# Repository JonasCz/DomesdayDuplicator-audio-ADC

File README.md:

# An experiment to add an audio ADC to the Domesday Duplicator (DdD)

An extension to the DdD to to add synced baseband audio support, with the DdD capture app writing it as a separate WAV file. Both PCM1802 (common module from china or custom board), or using the built-in adc128s102 that is already integrated on the DE0-nano board. PCM1802 has better quality, integrated ADC notably has a high noise floor at -40dB.

## Setup:

### You can use either:

**Custom board**: I designed a custom board, which has RCAs for both the PCM 1802, and the integrated adc128s102, allowing to use 4 channels at the same time if desired. Has better power regulator than PCM1802 modules (maybe lower noise), has a DIP switch for -10dB input level if needed.

Contact @Doohickey in Domesday86 discord, for around €20 + cheap shipping in europe.

**PCM1802 module**:

You can also use the low cost PCM1802 module. Connect with jumper wires, diagram:

Wires between pcm1802 and DdD should be as short as possible. You don't need to solder any of the fmt/mode/osr/bypass. Make sure the 3.3v on your module is working (3.3v is present), 3.3v needs to be connected to the pdw and fsy pins on the module. Connect lin/rin/gnd on the module to your audio source.

**adc128s102**:

Can be used with just some resistors and capacitors:

Resistors: any value between 1k and 10k works. Capacitor 1-10uF works. All capacitors and resistors need to be the same.

Can be used together with PCM1802 for 4 channels.

## Firmware:

You'll need to flash the firmware of the deo-nano, using the same process as for the initial flash. (firmware file in releases section). Note that there's no backward compatiblity, both the firmware and application need to be from this repository. Firmware from this repository won't work with old application either.

## Application:

Set your audio source in the application settings, then start capturing. It will write a wav file in the same location as the RF data, and show some statistics for the audio. The application is missing the logo in the UI because I couldn't get it to work, it's not intentionally removed :-)

(original readme follows)

# Domesday Duplicator (DdD)

Please see the [Project Wiki](https://github.com/simoninns/DomesdayDuplicator/wiki) for details of the project and for access to the project documentation.

The Domesday Duplicator is a LaserDisc capture focused, USB 3.0 based DAQ capable of 40 million samples per second acquisition of analogue RF data at 10-bits resolution, the data being in generic PCM style stream format is ready for [FLAC compression](https://github.com/oyvindln/vhs-decode/wiki/RF-Compression-&-Decompression-Guide) or direct use with a wide range of decoders.

Capture is via a easy to use GUI capture application.

# The Decode Family 

The samples the DdD capture can be used with the family of decoders that make the FM RF Archival workflow ready to use today.

[LaserDisc Decode](https://github.com/happycube/ld-decode) / [VHS-Decode (Videotape)](https://github.com/oyvindln/vhs-decode/wiki/) / [CVBS (Composite) Decode](CVBS-Composite-Decode) / [HiFi Decode](HiFi-Decode) / [RTLSDR HiFi Decode](RTLSDR) / [MUSE-Decode](https://bitbucket.org/staffanulfberg/ldaudio/src/master/musecpp/) / [CD-Decode](https://github.com/happycube/cd-decode) / [FL2K TBC Player](TBC-To-Analogue)

# 3D Printed Case 

The DomesDay Duplicator also has a [3D models](https://github.com/simoninns/DomesdayDuplicator-Case) and ready to use data for producing 3D printed cases, to protect from dust or line with copper tape for affordable EMI shielding for example.

## Authors

Domesday Duplicator was written & designed by [Simon Inns](https://github.com/simoninns).

Current documentation & fabrication is maintained by [Harry Munday](https://github.com/harrypm). 

## Licences

- [Software License - (Creative Commons BY-SA 4.0)](https://github.com/simoninns/DomesdayDuplicator/blob/master/LICENSE)
- [Hardware License - (GPLv3)](https://creativecommons.org/licenses/by-sa/4.0/)

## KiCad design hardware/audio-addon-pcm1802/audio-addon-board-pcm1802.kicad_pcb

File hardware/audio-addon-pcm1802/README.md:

# Audio capture and the PCM1802 add-on board

The Domesday Duplicator can record a player's baseband analogue audio at the same time as the
RF, written to separate files next to the RF capture. The audio is sampled in lock-step with
the RF: the gateware reads the audio converters once per 512-sample frame of the RF stream,
so the two can be lined up exactly afterwards without any clock-drift correction.

This needs three things:

1. one or both audio converters connected to the DE0-NANO (below);
2. the audio-capable application gateware, which sends the RF stream in the framed sample
   format (specified with the gateware, under [fpga/](../../fpga/)) instead of the plain
   sequence-counter format;
3. the capture application, with **File → Settings → Capture → Audio** set to the converters
   in use (or `--audio-source` on the command line).

With gateware that does not send the framed format, the capture application captures RF
exactly as before and reports that audio is not available from the device.

## Converters

There are two, and they can be used together for four channels.

| | PCM1802 | ADC128S022 |
| --- | --- | --- |
| Where | External — this add-on board, or a low-cost module | Already on the DE0-NANO |
| Resolution | 24-bit | 12-bit |
| Quality | The one to use | Noise floor around −40 dB; a fallback |
| Output file | `<capture>_audio_external_adc.s24` | `<capture>_audio_integrated_adc.s16` |

Both files are headerless, little-endian, interleaved stereo (left first). The sample rate is
the RF sample rate divided by 512: **78125 Hz** for a 40 MSPS capture, and **39062.5 Hz** when
the gateware's 2:1 decimation (20 MSPS) is on. The capture's metadata records the exact rate.

## The add-on board

This directory holds the design of a small board that plugs onto the DE0-NANO's 2x13 header
(JP3) and carries both audio paths:

- the **PCM1802** with RCA inputs, its own supply regulator and a DIP switch for a −10 dB
  input pad;
- RCA inputs and the bias network for the DE0-NANO's own **ADC128S022**.

| Path | Contents |
| --- | --- |
| `audio-addon-board-pcm1802.kicad_pro` / `.kicad_sch` / `.kicad_pcb` | KiCad 9 project: schematic and layout |
| `audio-addon-board-pcm1802-rounded.*` | The same layout with rounded tracks, generated by the round-tracks plugin |
| `parts/` | Symbols, footprints and 3D models that are not in the KiCad standard libraries |
| `production/` | Fabrication outputs for the built board: BOM, placement, designators and IPC netlist |
| `fabrication-toolkit-options.json`, `*.round-tracks-config` | Settings for the KiCad plugins that produced the above |
| `images/` | The photographs and wiring diagrams on this page |

### Connection to the DE0-NANO

All signals use the DE0-NANO's 2x13 header (JP3); nothing on the Duplicator main board
changes.

| Signal | Direction | JP3 pin | FPGA port | FPGA pin |
| --- | --- | --- | --- | --- |
| PCM1802 SCKI (system clock, 256·fs) | FPGA → ADC | 5 | `GPIO_2[0]` | `PIN_A14` |
| PCM1802 BCK (bit clock, 64·fs) | FPGA → ADC | 8 | `GPIO_2[3]` | `PIN_C16` |
| PCM1802 LRCK (frame clock, fs; high = left) | FPGA → ADC | 10 | `GPIO_2[5]` | `PIN_D16` |
| PCM1802 DOUT (data) | ADC → FPGA | 2 | `GPIO_2_IN[0]` | `PIN_E15` |
| ADC128S022 left input | analogue | — | `Analog_In0` | on-board ADC |
| ADC128S022 right input | analogue | — | `Analog_In1` | on-board ADC |

The PCM1802 runs in slave mode with left-justified 24-bit data, which is what its format and
mode pins select when left at their defaults.

## Without the board

### A PCM1802 module on jumper wires

The common low-cost PCM1802 module works. Keep the wires between the module and the
DE0-NANO as short as possible.

| Module pin | Connect to |
| --- | --- |
| SCK | JP3 pin 5 |
| BCK | JP3 pin 8 |
| LRCK | JP3 pin 10 |
| DOUT | JP3 pin 2 |
| GND | GND |
| +5V | a 5 V supply (the diagram takes it from the FX3 board) |

- **PDW and FSY must be tied to 3.3 V** (the module's own 3.3 V pin). Check that the module's
  3.3 V regulator is actually producing 3.3 V.
- FMT0/FMT1, MODE0/MODE1, OSR and BYPASS need no wiring.
- Connect the audio source to the module's LIN, RIN and GND.

### The on-board ADC128S022

Each channel needs two resistors as a divider from the header's 3.3 V to GND, biasing the
input at mid-supply, and a capacitor coupling the audio into the midpoint. Any resistor value
from 1 kΩ to 10 kΩ and any capacitor from 1 µF to 10 µF works, but use the same values for
every part. Left is `Analog_In0` and right is `Analog_In1`.

## In the capture application

**File → Settings → Capture → Audio** selects none, the integrated ADC (ADC128S022), the
external ADC (PCM1802), or both. The statistics panel shows the levels and clipping counts of the audio
being captured, and which stream format the device is sending.

A capture from framed-format gateware also carries a 48-bit sample counter, which is what
proves the capture has no gaps. By default a gap stops the capture, as it does for the
standard gateware. **Continue after dropped samples** (in the same settings page, or
`--on-dropped-samples continue`) instead counts the loss, resynchronises on the next frame and
carries on.

## Licence

The hardware design is licensed under **Creative Commons Attribution-ShareAlike 4.0
International**, the same as the main board. The full text is in
[../pcb/LICENSE.txt](../pcb/LICENSE.txt).

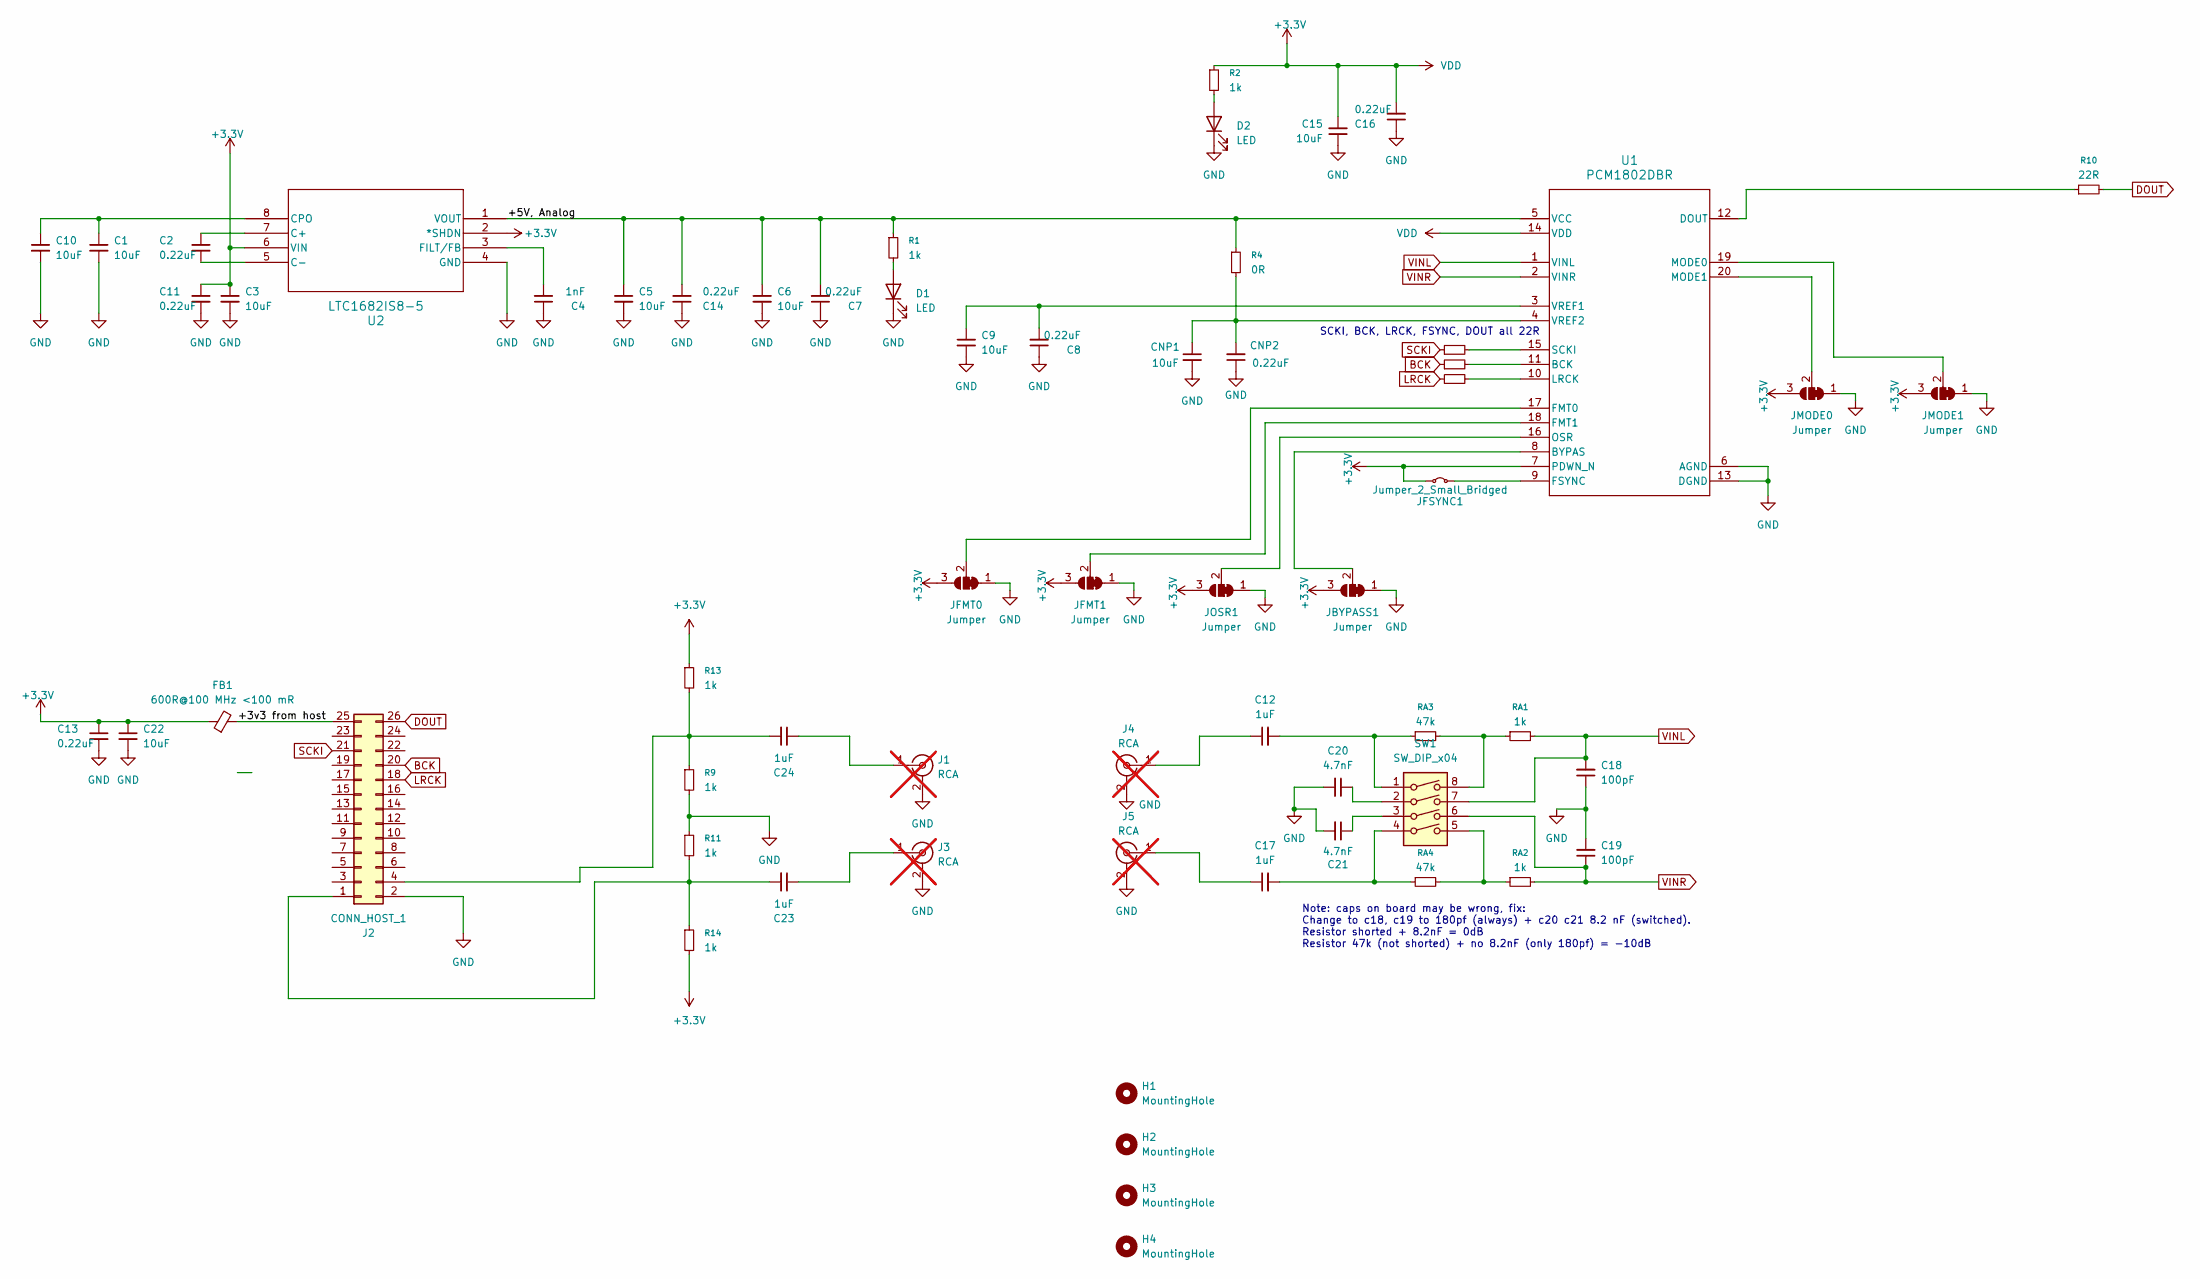
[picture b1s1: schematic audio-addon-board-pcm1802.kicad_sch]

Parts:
C1, C3, C5, C6, C9, C10, C15, C22: 10uF; C_0603_1608Metric; LCSC PN C96446
C2, C7, C8, C11, C13, C14, C16: 0.22uF; C_0603_1608Metric; LCSC PN C21120
C4: 1nF; C_0603_1608Metric; LCSC PN C1588
C12, C17, C23, C24: 1uF; C_0603_1608Metric; LCSC PN C15849
C18, C19: 100pF; C_0603_1608Metric; LCSC PN C14858
C20, C21: 4.7nF; C_0603_1608Metric; LCSC PN C53987
CNP1: 10uF; C_0603_1608Metric; LCSC PN C96446
CNP2: 0.22uF; C_0603_1608Metric; LCSC PN C21120
D1: LED; LED_0603_1608Metric
D2: LED; LED_0805_2012Metric
FB1: 600R@100 MHz <100 mR; L_0805_2012Metric; LCSC PN C1017
H1, H2, H3, H4: MountingHole; MountingHole_3.2mm_M3_DIN965_Pad_TopBottom
J1, J3, J4, J5: RCA; RCA-Phono_CUI-Devices_RCJ-01X_Horizontal; not fitted
J2: CONN_HOST_1; PinSocket_2x13_P2.54mm_Vertical
JBYPASS1: Jumper; SolderJumper-3_P1.3mm_Bridged12_RoundedPad1.0x1.5mm
JFMT0, JFMT1: Jumper; SolderJumper-3_P1.3mm_Bridged12_RoundedPad1.0x1.5mm
JFSYNC1: Jumper_2_Small_Bridged; SolderJumper-2_P1.3mm_Bridged_RoundedPad1.0x1.5mm
JMODE0, JMODE1: Jumper; SolderJumper-3_P1.3mm_Bridged12_RoundedPad1.0x1.5mm
JOSR1: Jumper; SolderJumper-3_P1.3mm_Bridged12_RoundedPad1.0x1.5mm
R1, R2: 1k; R_0603_1608Metric; LCSC PN C21189
R4: 0R; R_0603_1608Metric; LCSC PN C21189
R5, R6, R7, R10: 22R; R_0603_1608Metric; LCSC PN C23345
R9, R11, R13, R14: 1k; R_0603_1608Metric; LCSC PN C21190
RA1, RA2: 1k; R_0603_1608Metric; LCSC PN C21190
RA3, RA4: 47k; R_0603_1608Metric; LCSC PN C25819
SW1: SW_DIP_x04; SW_DIP_SPSTx04_Slide_Copal_CHS-04B_W7.62mm_P1.27mm; LCSC PN C319050
U1: PCM1802DBR; DB0020A-MFG; LCSC PN C1520787
U2: LTC1682IS8-5; SO-8_S_LIT; LCSC PN C676404

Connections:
+3.3V: C3.1, C11.1, C13.1, C15.2, C16.2, C22.1, FB1.1, JBYPASS1.3 (B), JFMT0.3 (B), JFMT1.3 (B), JFSYNC1.1 (A), JMODE0.3 (B), JMODE1.3 (B), JOSR1.3 (B), R2.1, R13.1, R14.2, U1.7 (PDWN_N), U1.14 (VDD), U2.2 (*SHDN), U2.6 (VIN)
/+3v3 from host: FB1.2, J2.25
/+5V, Analog: C5.1, C6.1, C7.2, C14.2, R1.1, R4.1, U1.5 (VCC), U2.1 (VOUT)
BCK: J2.20, R6.1
DOUT: J2.26, R10.2
GND: C1.2, C3.2, C4.1, C5.2, C6.2, C7.1, C8.1, C9.2, C10.2, C11.2, C13.2, C14.1, C15.1, C16.1, C18.1, C19.2, C20.2, C21.2, C22.2, CNP1.2, CNP2.1, D1.1 (K), D2.1 (K), J1.2 (Ext), J2.2, J3.2 (Ext), J4.2 (Ext), J5.2 (Ext), JBYPASS1.1 (A), JFMT0.1 (A), JFMT1.1 (A), JMODE0.1 (A), JMODE1.1 (A), JOSR1.1 (A), R9.2, R11.1, U1.6 (AGND), U1.13 (DGND), U2.4 (GND)
LRCK: J2.18, R7.1
unnamed: C12.2, RA3.1, SW1.1
unnamed: C17.2, RA4.1, SW1.4
unnamed: C20.1, SW1.2
unnamed: C21.1, SW1.3
unnamed: D1.2 (A), R1.2
unnamed: D2.2 (A), R2.2
unnamed: C24.1, J1.1 (In)
unnamed: C23.2, J2.1, R11.2, R14.1
unnamed: C24.2, J2.4, R9.1, R13.2
unnamed: C23.1, J3.1 (In)
unnamed: C12.1, J4.1 (In)
unnamed: C17.1, J5.1 (In)
unnamed: JBYPASS1.2 (C), U1.8 (BYPAS)
unnamed: JFMT0.2 (C), U1.17 (FMT0)
unnamed: JFMT1.2 (C), U1.18 (FMT1)
unnamed: JFSYNC1.2 (B), U1.9 (FSYNC)
unnamed: JMODE0.2 (C), U1.20 (MODE1)
unnamed: JMODE1.2 (C), U1.19 (MODE0)
unnamed: JOSR1.2 (C), U1.16 (OSR)
unnamed: RA1.1, RA3.2, SW1.8
unnamed: RA2.1, RA4.2, SW1.5
unnamed: R6.2, U1.11 (BCK)
unnamed: R10.1, U1.12 (DOUT)
unnamed: R7.2, U1.10 (LRCK)
unnamed: R5.2, U1.15 (SCKI)
unnamed: C8.2, C9.1, U1.3 (VREF1)
unnamed: CNP1.1, CNP2.2, R4.2, U1.4 (VREF2)
unnamed: C2.1, U2.7 (C+)
unnamed: C2.2, U2.5 (C-)
unnamed: C1.1, C10.1, U2.8 (CPO)
unnamed: C4.2, U2.3 (FILT/FB)
SCKI: J2.21, R5.1
VINL: C18.2, RA1.2, SW1.7, U1.1 (VINL)
VINR: C19.1, RA2.2, SW1.6, U1.2 (VINR)

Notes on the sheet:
Note: caps on board may be wrong, fix: Change to c18, c19 to 180pf (always) + c20 c21 8.2 nF (switched). Resistor shorted + 8.2nF = 0dB Resistor 47k (not shorted) + no 8.2nF (only 180pf) = -10dB
SCKI, BCK, LRCK, FSYNC, DOUT all 22R

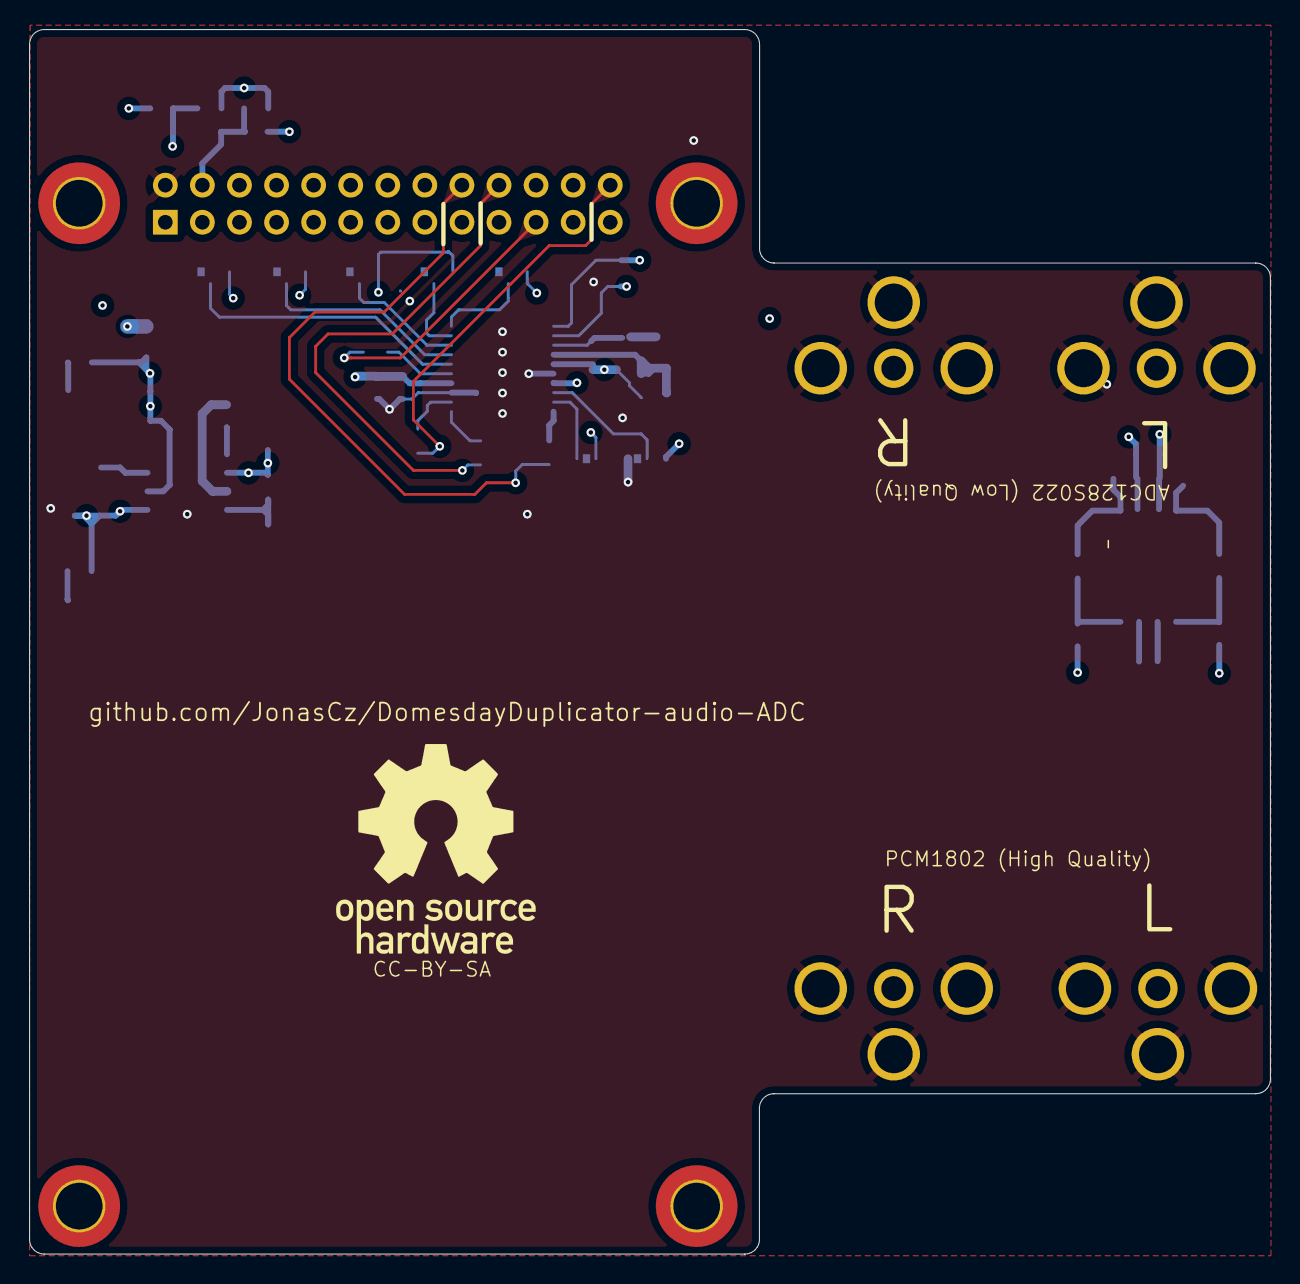
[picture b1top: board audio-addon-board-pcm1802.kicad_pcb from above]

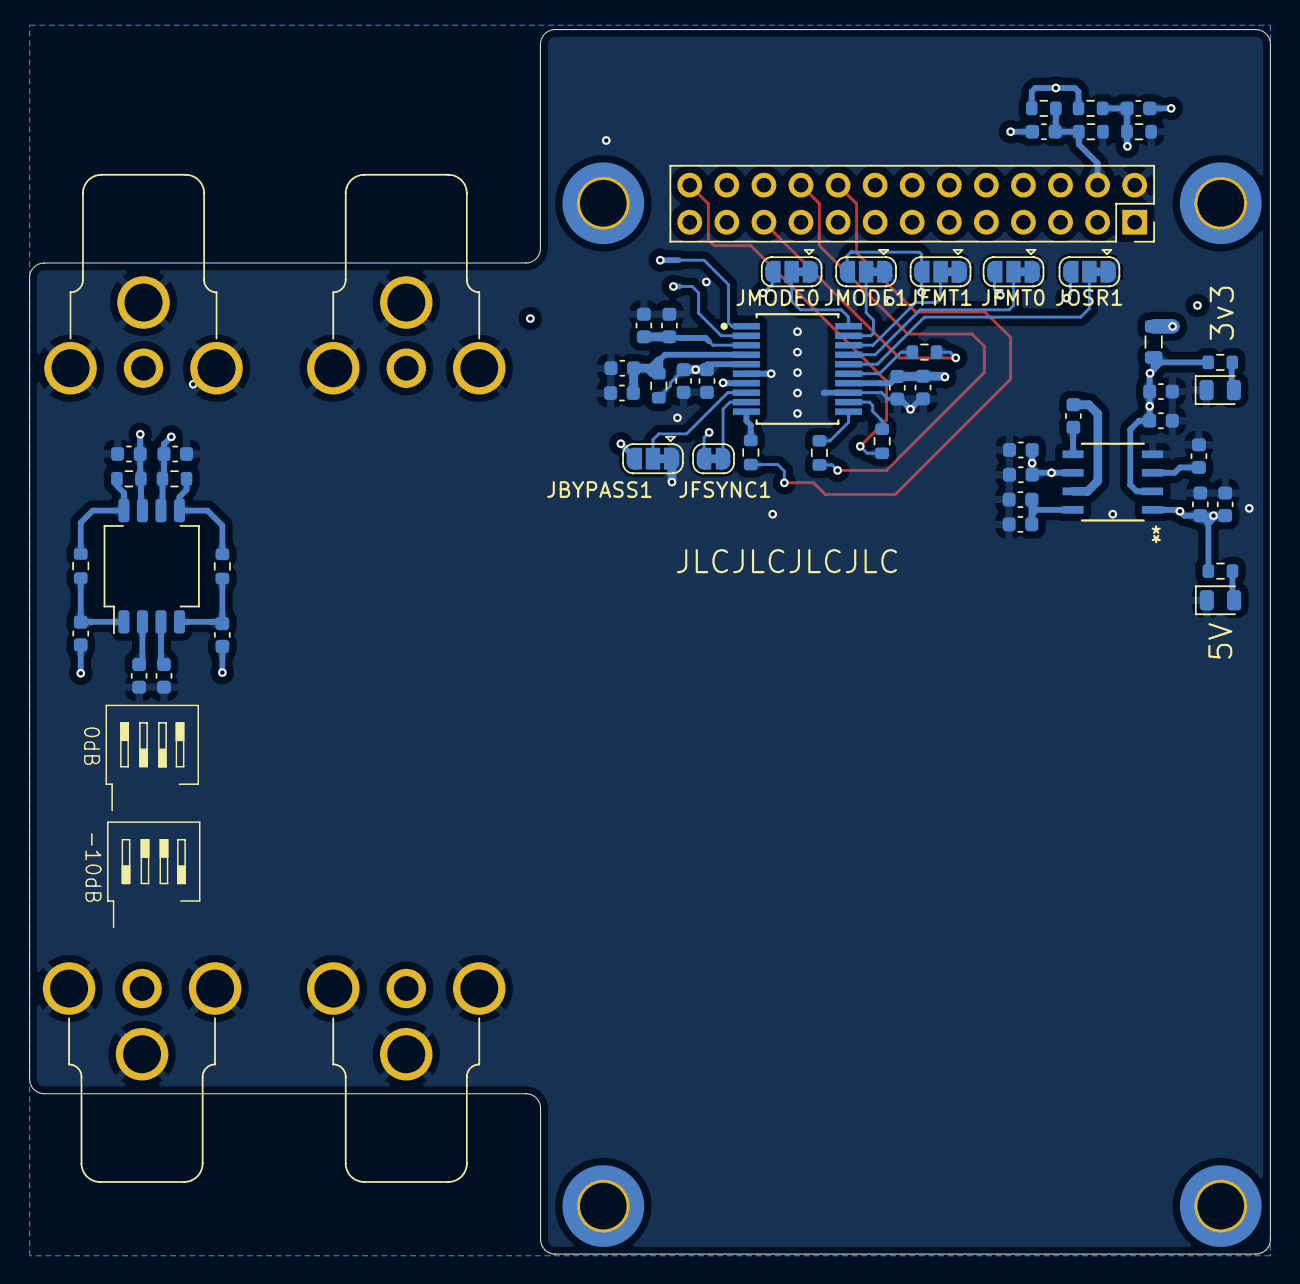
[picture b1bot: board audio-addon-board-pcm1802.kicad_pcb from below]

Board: 4 copper layers, 85.0 x 83.9 mm, 63 parts (59 on the bottom side), 41 nets.

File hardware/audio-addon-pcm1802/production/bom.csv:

Designator,Footprint,Quantity,Value,LCSC Part #
"C1, C10, C15, C22, C3, C5, C6, C9, CNP1",0603,9,10uF,C96446
"C11, C13, C14, C16, C2, C7, C8, CNP2",0603,8,0.22uF,C21120
"C12, C17, C23, C24",0603,4,1uF,C15849
"C18, C19",0603,2,100pF,C14858
"C20, C21",0603,2,4.7nF,C53987
C4,0603,1,1nF,C1588
"D1, D2",0805,2,LED,
FB1,0805,1,600R@100 MHz <100 mR,C1017
J2,PinSocket_2x13_P2.54mm_Vertical,1,CONN_HOST_1,
JFSYNC1,SolderJumper-2_P1.3mm_Bridged_RoundedPad1.0x1.5mm,1,Jumper_2_Small_Bridged,
"R1, R2",0603,2,1k,C21189
"R10, R5, R6, R7",0603,4,22R,C23345
"R11, R13, R14, R9, RA1, RA2",0603,6,1k,C21190
R4,0603,1,0R,C21189
"RA3, RA4",0603,2,47k,C25819
SW1,SW_DIP_SPSTx04_Slide_Copal_CHS-04B_W7.62mm_P1.27mm,1,SW_DIP_x04,C319050
U1,DB0020A-MFG,1,PCM1802DBR,C1520787
U2,SO-8_S_LIT,1,LTC1682IS8-5,C676404

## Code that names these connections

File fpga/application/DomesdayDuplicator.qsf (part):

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#============================================================
# GPIO_2, the 2x13 header JP3
#============================================================
# Carries the PCM1802: SCKI on GPIO_2[0] (JP3 pin 5), BCK on GPIO_2[3]
# (pin 8), LRCK on GPIO_2[5] (pin 10) and DOUT on GPIO_2_IN[0] (pin 2).
# Every other pin is high-Z. Names and locations are Terasic's - their
# reference .qsf and the user manual's Table 3-8 - and the header pin
# numbers are from the board schematic. GPIO_2_IN[2:0] are input-only.
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
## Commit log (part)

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2025-10-04 add LLM plan for audio
2025-10-04 add LLM docs
2025-10-04 build and run scripts (LLM)
2025-10-04 inital on-board audio ADC implementation (LLM)
2025-10-05 inital application implementation
2025-10-05 fixes, comment out the seq number for now
2025-10-05 update gitignore
2025-10-05 add build scripts
2025-10-06 add debug code
2025-10-06 fix dc offset
2025-10-06 fix to have same ADC channels always
2025-10-06 brute-force solution to not connecting: just retry
2025-10-06 initial semi-working pcm1802
2025-10-06 working!
2025-10-06 fix -6dB amplitude
2025-10-07 add intial PCB progress
2025-10-07 working on layout
2025-10-09 working on layout (2025-10-09 sent to jlc)
2025-10-15 more work on the software for audio capture
2025-10-16 docs
2025-10-16 add note to fix cap values
2025-10-16 try to fix the logo (unsuccessfully)
2025-10-16 add stuff to gitignore
2025-10-16 fix lag
2025-10-17 gitignore more stuff
2025-10-20 update schematic
2025-10-23 initial board fixes
2025-10-27 board fixes, finished
2025-10-28 board fixes
2025-11-08 try to fix build on linux
2025-11-17 update board
2025-11-17 update board photo
2025-11-17 fix typo (to not have conflicts with upstream)
2025-11-17 move readme
2025-11-18 move the readme text back
2025-11-29 fix config ui item height
2025-11-29 use headerless raw file instead
2025-11-29 ignore sync loss
2025-12-11 UI fix for sync loss ignore
2025-12-12 Add WinUSB toggle functionality to configuration dialog
2025-12-12 fix text

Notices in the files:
hardware/audio-addon-pcm1802/audio-addon-board-pcm1802.kicad_pcb:
CC-BY-SA
